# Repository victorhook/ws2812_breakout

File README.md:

# Super Simple WS2812 Breakout PCB

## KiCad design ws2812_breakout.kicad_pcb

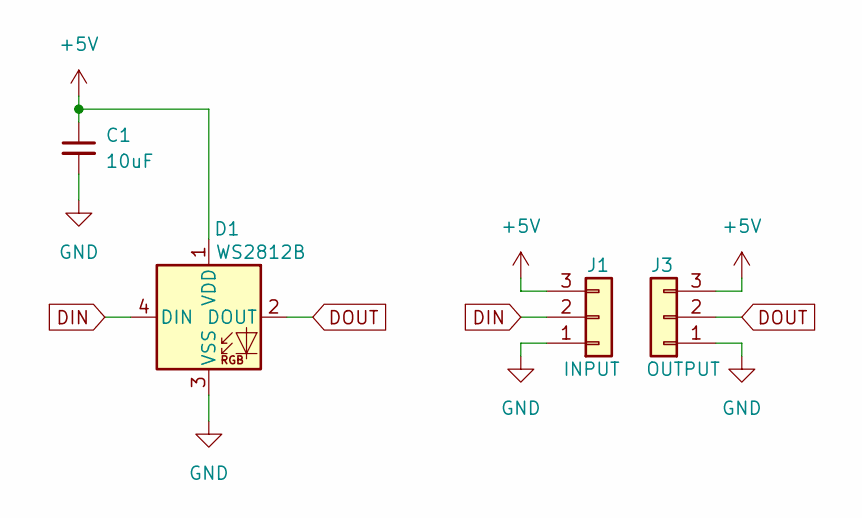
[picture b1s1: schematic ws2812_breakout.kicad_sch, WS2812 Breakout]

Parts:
C1: 10uF; C_0603_1608Metric_NoSilk
D1: WS2812B; LED_WS2812B_PLCC4_5.0x5.0mm_P3.2mm_NoSilk
J1: INPUT; Conn_3_2_SMD
J3: OUTPUT; Conn_3_2_SMD

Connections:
+5V: C1.1, D1.1 (VDD), J1.3, J3.3
DIN: D1.4 (DIN), J1.2
DOUT: D1.2 (DOUT), J3.2
GND: C1.2, D1.3 (VSS), J1.1, J3.1

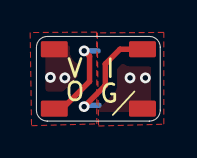
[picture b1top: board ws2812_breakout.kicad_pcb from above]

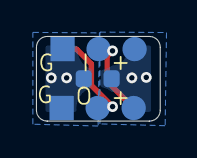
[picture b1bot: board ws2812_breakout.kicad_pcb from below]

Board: 2 copper layers, 6.9 x 4.7 mm, 4 parts (3 on the bottom side), 4 nets.

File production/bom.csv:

Designator,Footprint,Quantity,Value,LCSC Part #
C1,0603,1,10uF,
D1,LED_WS2812B_PLCC4_5.0x5.0mm_P3.2mm_NoSilk,1,WS2812B,
J1,Conn_3_2_SMD,1,INPUT,
J3,Conn_3_2_SMD,1,OUTPUT,

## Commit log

2024-11-10 Rev A ready for order!
